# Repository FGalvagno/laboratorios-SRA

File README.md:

# Laboratorios SRA 2024
Este repositorio cuenta con los laboratorios de la asignatura Síntesis de Redes Activas, de la carrera de Ingeniería en Electrónica de la FCEFyN - UNC.

1. Amplificadores Operacionales Ideales
2. Amplificadores Operacionales Reales
3. Diseño de Amplificadores
4. Filtros Activos

# Instalación dependencias de Python
En los trabajos se utilizó Python como herramienta de apoyo para el calculo y gráfico.

## Requisitos previos

Para ejecutar los script de este repositorio, se necesita:

1. **Python 3.7 o una versión más reciente**: Descárgalo desde el [sitio web oficial de Python](https://www.python.org/downloads/).
2. **Librerías requeridas**:
   - `scipy`
   - `numpy`
   - `matplotlib`
   - `plotly`

Las dependencias se pueden instalar usando PIP
```bash
pip install scipy numpy matplotlib plotly
```

# LTSpice

Las simulaciones expuestas en el presente repositorio fueron realizadas utilizando LTspice de Analog Devices, para mas información ingresar a su [sitio web](https://www.analog.com/en/resources/design-tools-and-calculators/ltspice-simulator.html)

# Kicad

Algunos de los trabajos realizados requirieron el desarrollo de placas de circuito impreso (PCB). Se uso Kicad 8.0.6 para esta finalidad. Para más información, visite el [sitio web](kicad.org) del proyecto.

## BOM de los proyectos realizados
Los BOM de las placas diseñadas se pueden encontrar en sus respectivas carpetas:
- [BOM TP1](https://htmlpreview.github.io/?https://github.com/FGalvagno/laboratorios-SRA/blob/main/LABN1_SRA/kicad/LABN1_SRA/bom/ibom.html)
- [BOM TP2](https://htmlpreview.github.io/?https://github.com/FGalvagno/laboratorios-SRA/blob/main/LABN2_SRA/kicad/LABN2_SRA/bom/ibom.html)

# Tutoriales

En este apartado del repositorio se colocará el acceso a diferentes tutoriales en video realizados por los estudiantes que profundizan un poco acerca del uso de las herramientas utilizadas para el desarrollo de las actividades.

## LTspice
- [Primer Tutorial: Instalación y Configuración de LTSpice + Componentes y Herramientas Incluidas](https://www.youtube.com/watch?v=8eU4OkuLDko)
- [Segundo Tutorial: Cómo Crear un Amplificador Sumador Inversor en LTSpice](https://www.youtube.com/watch?v=xFDNSKlyUxU)
- [Tercer Tutorial: Simulación en LTSpice + Diagramas de Fase y Bode](https://www.youtube.com/watch?v=1XbrADAF3E8)

## Kicad
- [Primer Tutorial  - Instalación de Kicad en Linux y Windows](https://youtu.be/r6Cftlv0W8k)
- [Segundo Tutorial  - Utilización de Kicad para realizar esquemáticos](https://youtu.be/AmCJIVljmYw)
- [Tercer Tutorial  - Asignación de huellas y exportación de componentes al PCB](https://youtu.be/4QtPsmXvcmw)
- [Cuarto Tutorial - Creación de PCB usando Kicad](https://youtu.be/VFZ34iJKWYY)

# Componentes Utilizados - Datasheets
Esta sección contiene enlaces a los últimos datasheets disponibles de cada integrado.

- [LM324](https://www.ti.com/lit/gpn/lm324)
- [TL072](https://www.ti.com/mx/lit/gpn/tl072)
- [LM6181](https://www.mouser.com/ds/2/405/snos634c-522069.pdf)

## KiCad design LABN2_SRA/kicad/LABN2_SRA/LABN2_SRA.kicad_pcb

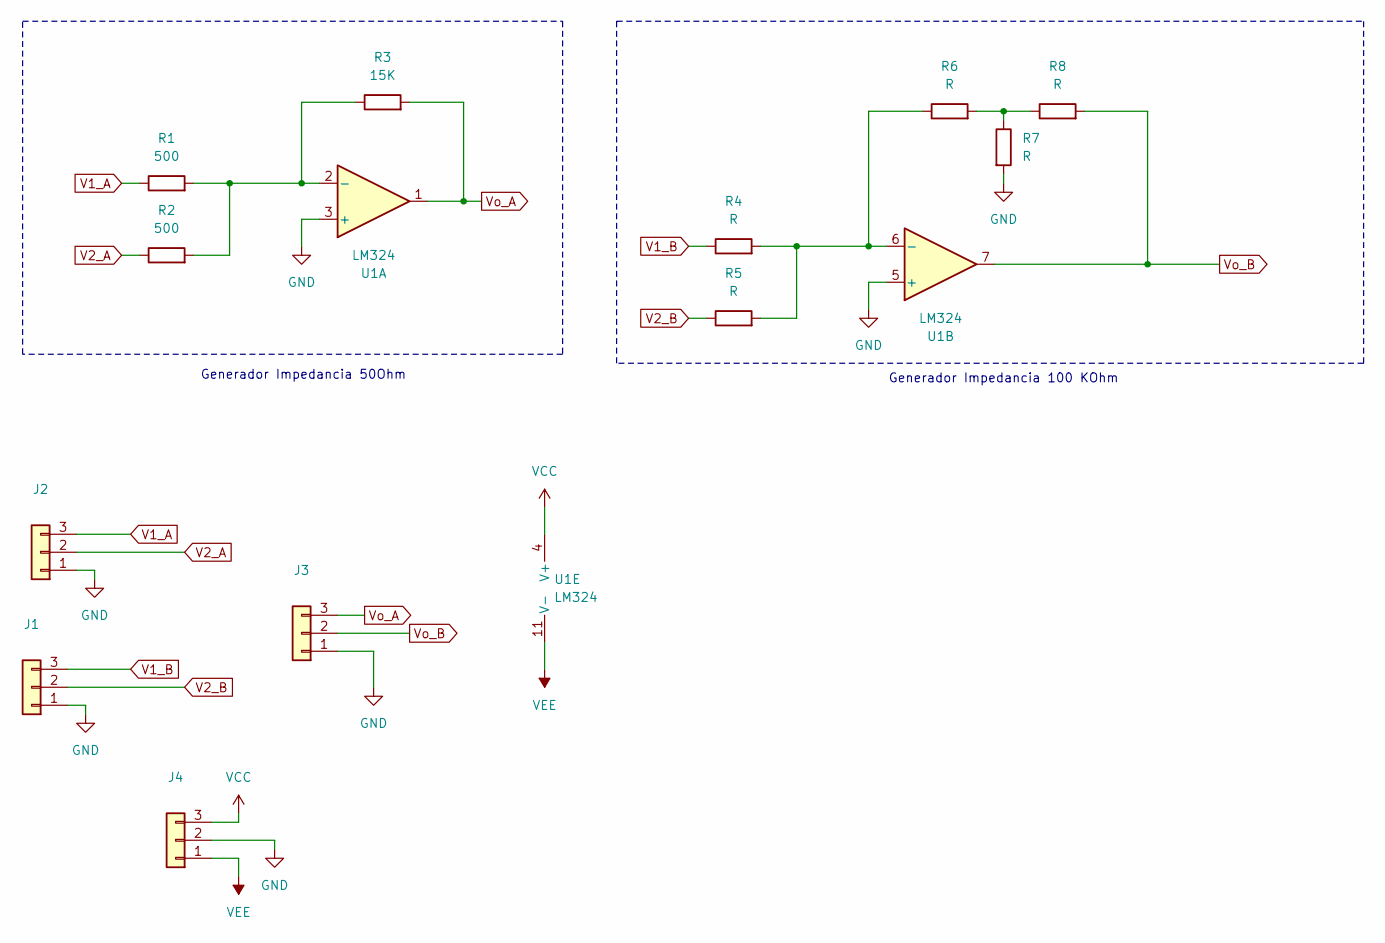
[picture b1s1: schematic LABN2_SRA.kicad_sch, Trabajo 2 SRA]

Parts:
J1, J2, J3, J4: Conn_01x03; PinHeader_1x03_P2.54mm_Vertical
R1, R2: 500; R_Axial_DIN0309_L9.0mm_D3.2mm_P15.24mm_Horizontal
R3: 15K; R_Axial_DIN0309_L9.0mm_D3.2mm_P15.24mm_Horizontal
R4, R5, R6, R7, R8: R; R_Axial_DIN0309_L9.0mm_D3.2mm_P15.24mm_Horizontal
U1: LM324; DIP-14_W7.62mm_Socket_LongPads

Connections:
GND: J1.1, J2.1, J3.1, J4.2, R7.2, U1.3 (+), U1.5 (+)
unnamed: R6.2, R7.1, R8.1
unnamed: R1.2, R2.2, R3.1, U1.2 (-)
unnamed: R4.2, R5.2, R6.1, U1.6 (-)
V1_A: J2.3, R1.1
V1_B: J1.3, R4.1
V2_A: J2.2, R2.1
V2_B: J1.2, R5.1
VCC: J4.3, U1.4 (V+)
VEE: J4.1, U1.11 (V-)
Vo_A: J3.3, R3.2, U1.1
Vo_B: J3.2, R8.2, U1.7

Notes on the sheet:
Generador Impedancia 100 KOhm
Generador Impedancia 50Ohm

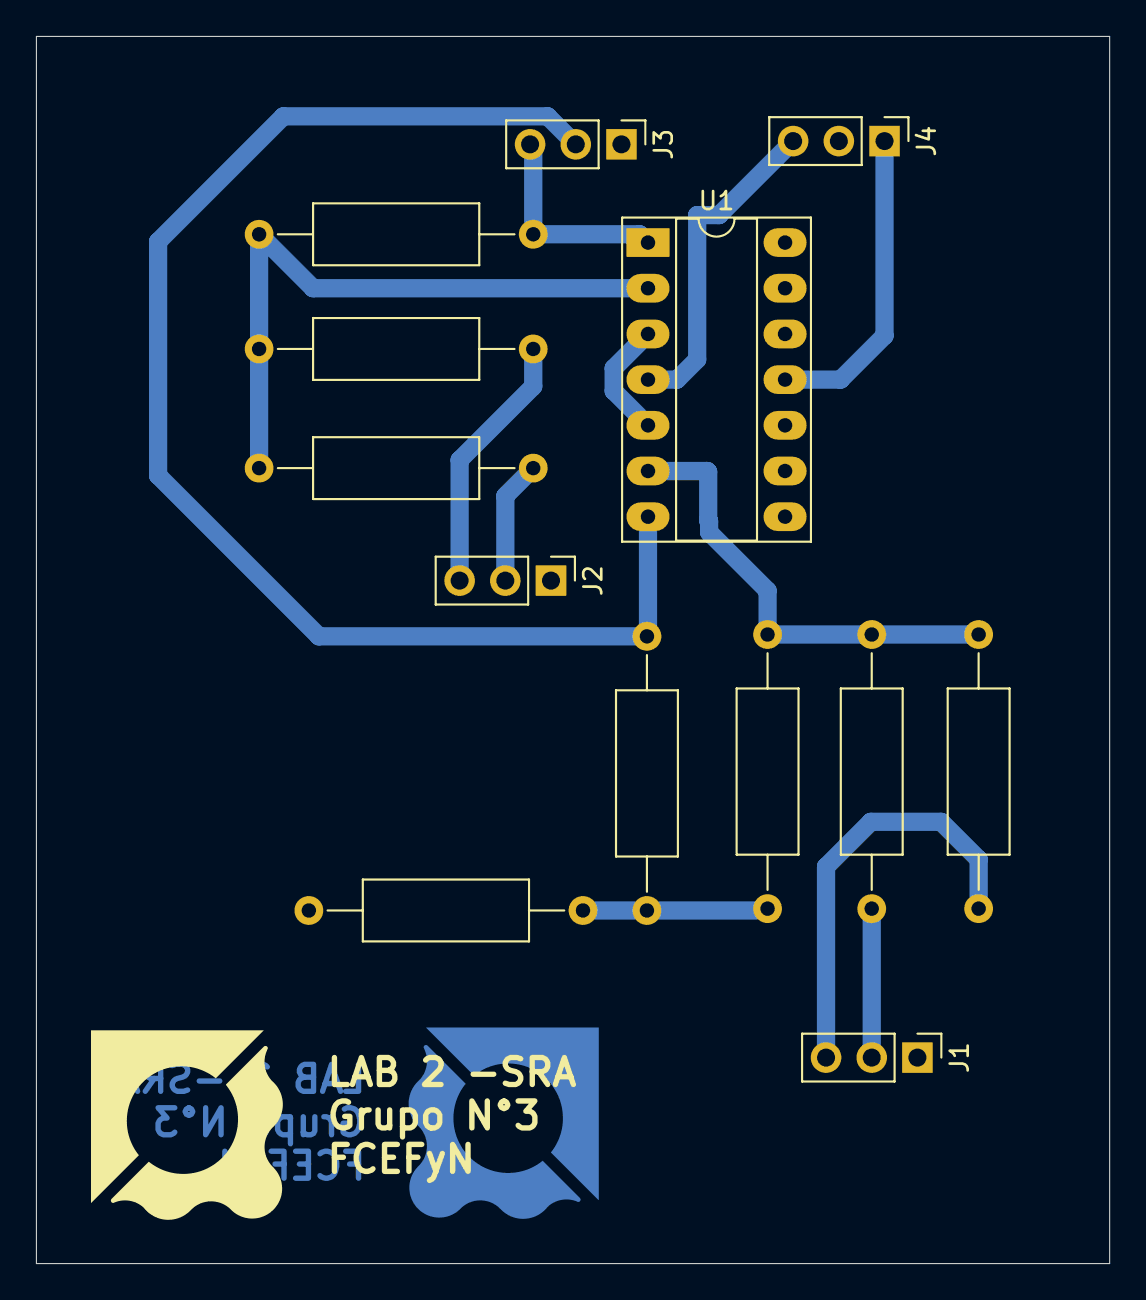
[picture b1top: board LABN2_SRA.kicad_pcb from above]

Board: 2 copper layers, 59.7 x 68.2 mm, 13 parts (0 on the bottom side), 12 nets.

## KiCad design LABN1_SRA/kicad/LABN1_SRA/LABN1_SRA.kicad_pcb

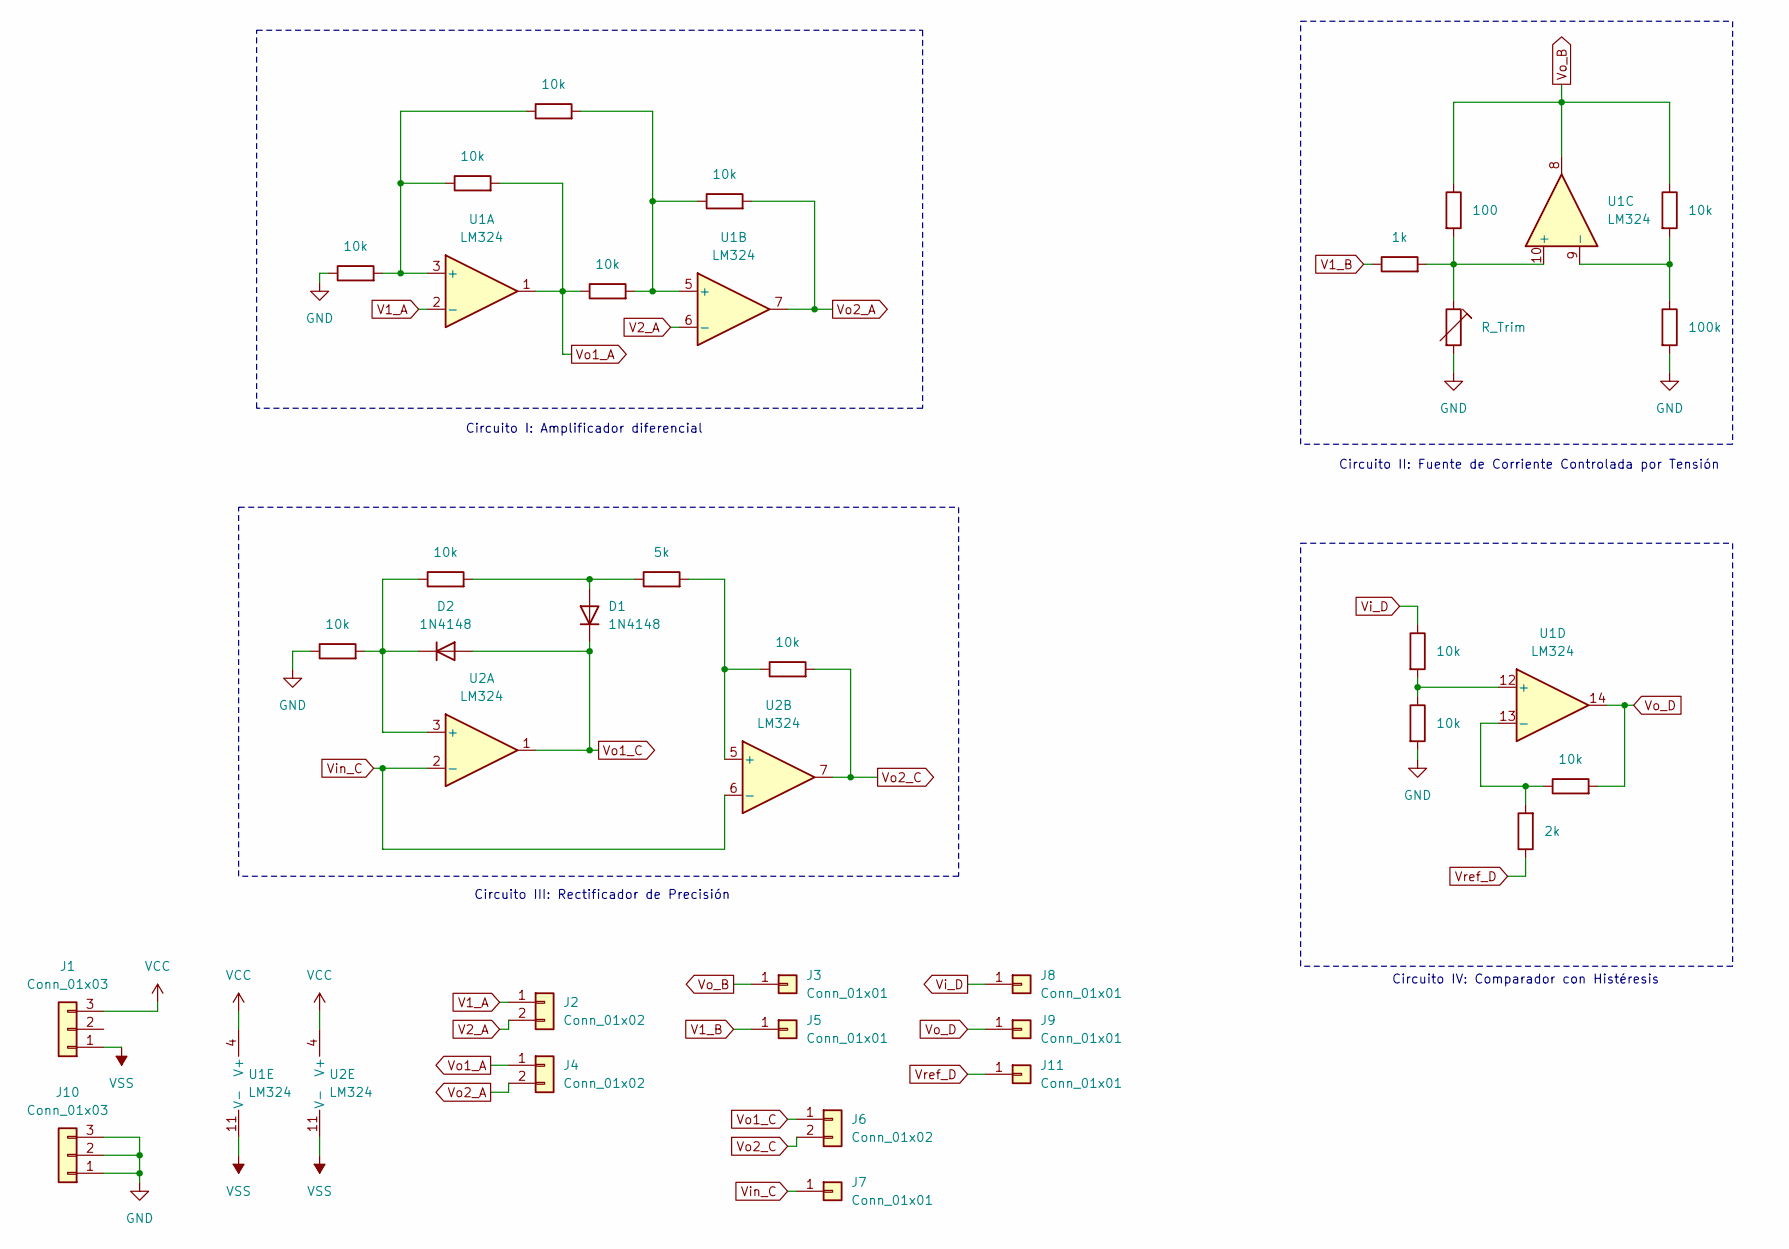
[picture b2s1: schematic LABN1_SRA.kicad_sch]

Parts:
D1, D2: 1N4148; D_DO-35_SOD27_P7.62mm_Horizontal
J1, J10: Conn_01x03; PinHeader_1x03_P2.54mm_Vertical
J2, J4, J6: Conn_01x02; PinHeader_1x02_P2.54mm_Vertical
J3, J5, J7, J8, J9, J11: Conn_01x01; PinHeader_1x01_P2.54mm_Vertical
R1, R2, R3, R4, R5, R7, R11, R12, R14, R15, R16, R18: 10k; R_Axial_DIN0309_L9.0mm_D3.2mm_P15.24mm_Horizontal
R6: 100; R_Axial_DIN0309_L9.0mm_D3.2mm_P15.24mm_Horizontal
R9: 100k; R_Axial_DIN0309_L9.0mm_D3.2mm_P15.24mm_Horizontal
R10: 1k; R_Axial_DIN0309_L9.0mm_D3.2mm_P15.24mm_Horizontal
R13: 5k; R_Axial_DIN0309_L9.0mm_D3.2mm_P15.24mm_Horizontal
R17: 2k; R_Axial_DIN0309_L9.0mm_D3.2mm_P15.24mm_Horizontal
R19: R_Trim; Potentiometer_ACP_CA9-H3,8_Horizontal
U1, U2: LM324; CERDIP-14_W7.62mm_SideBrazed_LongPads_Socket

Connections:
GND: J10.1, J10.2, J10.3, R1.1, R9.2, R12.1, R16.2, R19.2
unnamed: D1.2 (A), R11.2, R13.1
unnamed: D2.1 (K), R11.1, R12.2, U2.3 (+)
unnamed: R1.2, R2.1, R3.1, U1.3 (+)
unnamed: R3.2, R4.2, R5.1, U1.5 (+)
unnamed: R6.2, R10.2, R19.1, U1.10 (+)
unnamed: R7.2, R9.1, U1.9 (-)
unnamed: R15.2, R16.1, U1.12 (+)
unnamed: R17.2, R18.1, U1.13 (-)
unnamed: R13.2, R14.1, U2.5 (+)
V1_A: J2.1, U1.2 (-)
V1_B: J5.1, R10.1
V2_A: J2.2, U1.6 (-)
VCC: J1.3, U1.4 (V+), U2.4 (V+)
VSS: J1.1, U1.11 (V-), U2.11 (V-)
Vi_D: J8.1, R15.1
Vin_C: J7.1, U2.2 (-), U2.6 (-)
Vo1_A: J4.1, R2.2, R4.1, U1.1
Vo1_C: D1.1 (K), D2.2 (A), J6.1, U2.1
Vo2_A: J4.2, R5.2, U1.7
Vo2_C: J6.2, R14.2, U2.7
Vo_B: J3.1, R6.1, R7.1, U1.8
Vo_D: J9.1, R18.2, U1.14
Vref_D: J11.1, R17.1

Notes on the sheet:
Circuito I: Amplificador diferencial
Circuito IV: Comparador con Histéresis
Circuito III: Rectificador de Precisión
Circuito II: Fuente de Corriente Controlada por Tensión

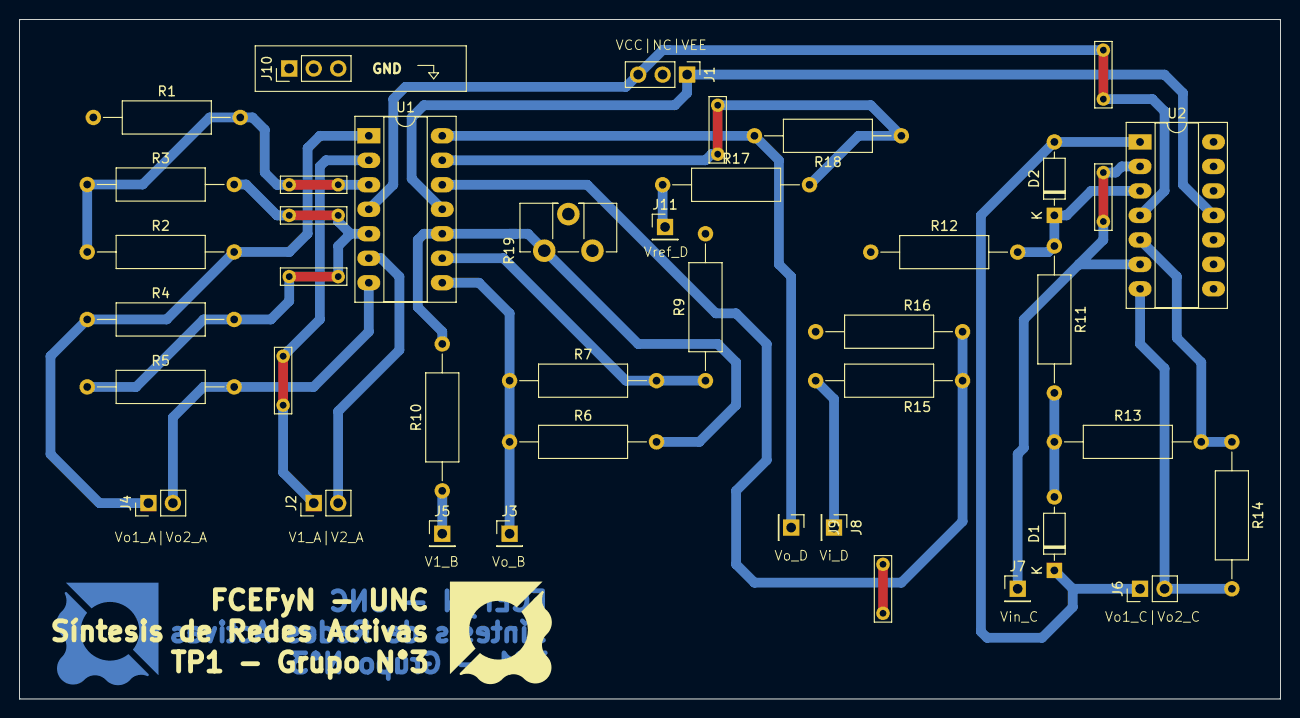
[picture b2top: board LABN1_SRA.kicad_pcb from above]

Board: 2 copper layers, 130.8 x 70.5 mm, 33 parts (0 on the bottom side), 24 nets.

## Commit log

2024-11-16 Lab N1
2024-11-17 Lab N2
2024-11-17 LTSpice data
2024-11-17 Agrego graficos al circuito 1 del TP1
2024-11-17 add kicad
2024-11-18 update lab1
2024-11-18 Add LTSpice data and scripts
2024-11-18 updated kicad files
2024-11-19 added python script for chebyshev filter coef.
2024-11-19 Add LTSpice data, scripts and update .tex
2024-11-19 update tp3
2024-11-21 updated kicad
2024-11-22 Create LTSpice_circuitos
2024-11-27 add files
2024-11-27 upload TP3/TP4 scripts
2024-11-29 informes actualizados
2025-02-16 añadida BOM
2025-02-16 added bom TP2
2025-02-16 updated ibom.html TP2
2025-02-16 updated ibom.html TP1
2025-02-16 updated ibom TP2
2025-02-16 actualizados archivos kicad a la ultima version
2025-02-17 update route
2025-02-17 añadido pdf LABN1
2025-02-17 añadido pdf LABN2
2025-02-17 añadido pdf LABN3
2025-02-17 añadido pdf LABN4
2025-02-17 añadido informe LABN3
2025-02-17 upload LTSpice_circuitos
